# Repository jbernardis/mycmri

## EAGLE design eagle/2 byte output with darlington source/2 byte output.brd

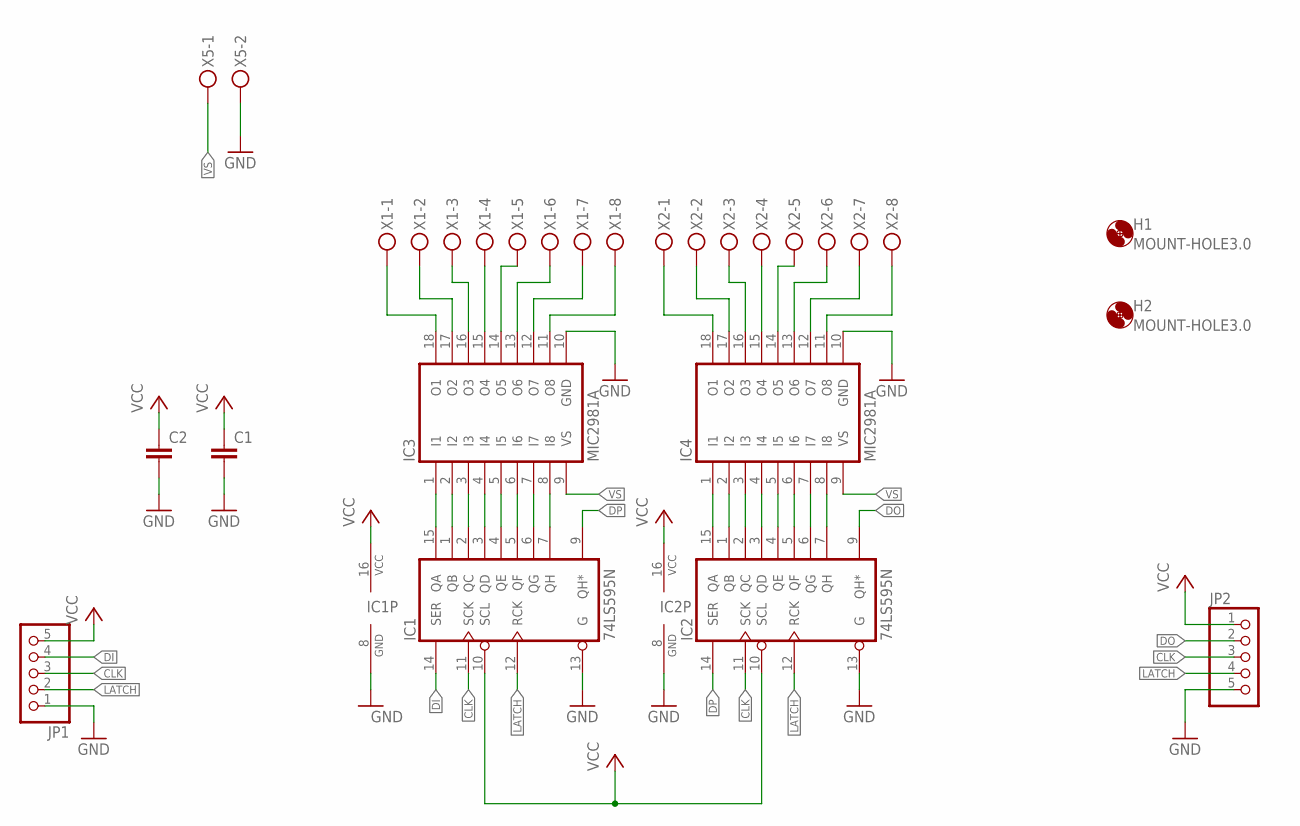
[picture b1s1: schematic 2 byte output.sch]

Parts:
C1, C2: C-EU050-035X075; C050-035X075
H1, H2: MOUNT-HOLE3.0; 3,0
IC1, IC2: 74LS595N; DIL16
IC3, IC4: MIC2981A; DIL18
JP1, JP2: PINHD-1X5/90; 1X05/90
X1, X2: MKDSN1,5/8-5,08
X5: MKDSN1,5/2-5,08

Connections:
CLK: IC1.11 (SCK), IC2.11 (SCK), JP1.3, JP2.3
DI: IC1.14 (SER), JP1.4
DO: IC2.9 (QH*), JP2.2
DP: IC1.9 (QH*), IC2.14 (SER)
GND: C1.2, C2.2, IC1.8 (GND), IC1.13 (G), IC2.8 (GND), IC2.13 (G), IC3.10 (GND), IC4.10 (GND), JP1.1, JP2.5, X5.2
LATCH: IC1.12 (RCK), IC2.12 (RCK), JP1.2, JP2.4
unnamed: IC3.15 (O4), X1.4
unnamed: IC3.16 (O3), X1.3
unnamed: IC3.17 (O2), X1.2
unnamed: IC3.18 (O1), X1.1
unnamed: IC3.14 (O5), X1.5
unnamed: IC3.12 (O7), X1.7
unnamed: IC3.11 (O8), X1.8
unnamed: IC3.13 (O6), X1.6
unnamed: IC4.15 (O4), X2.4
unnamed: IC4.16 (O3), X2.3
unnamed: IC4.17 (O2), X2.2
unnamed: IC4.18 (O1), X2.1
unnamed: IC4.14 (O5), X2.5
unnamed: IC4.13 (O6), X2.6
unnamed: IC4.12 (O7), X2.7
unnamed: IC4.11 (O8), X2.8
unnamed: IC1.15 (QA), IC3.1 (I1)
unnamed: IC1.1 (QB), IC3.2 (I2)
unnamed: IC1.2 (QC), IC3.3 (I3)
unnamed: IC1.3 (QD), IC3.4 (I4)
unnamed: IC1.4 (QE), IC3.5 (I5)
unnamed: IC1.5 (QF), IC3.6 (I6)
unnamed: IC1.6 (QG), IC3.7 (I7)
unnamed: IC1.7 (QH), IC3.8 (I8)
unnamed: IC2.15 (QA), IC4.1 (I1)
unnamed: IC2.1 (QB), IC4.2 (I2)
unnamed: IC2.2 (QC), IC4.3 (I3)
unnamed: IC2.3 (QD), IC4.4 (I4)
unnamed: IC2.4 (QE), IC4.5 (I5)
unnamed: IC2.5 (QF), IC4.6 (I6)
unnamed: IC2.6 (QG), IC4.7 (I7)
unnamed: IC2.7 (QH), IC4.8 (I8)
VCC: C1.1, C2.1, IC1.10 (SCL), IC1.16 (VCC), IC2.10 (SCL), IC2.16 (VCC), JP1.5, JP2.1
VS: IC3.9 (VS), IC4.9 (VS), X5.1

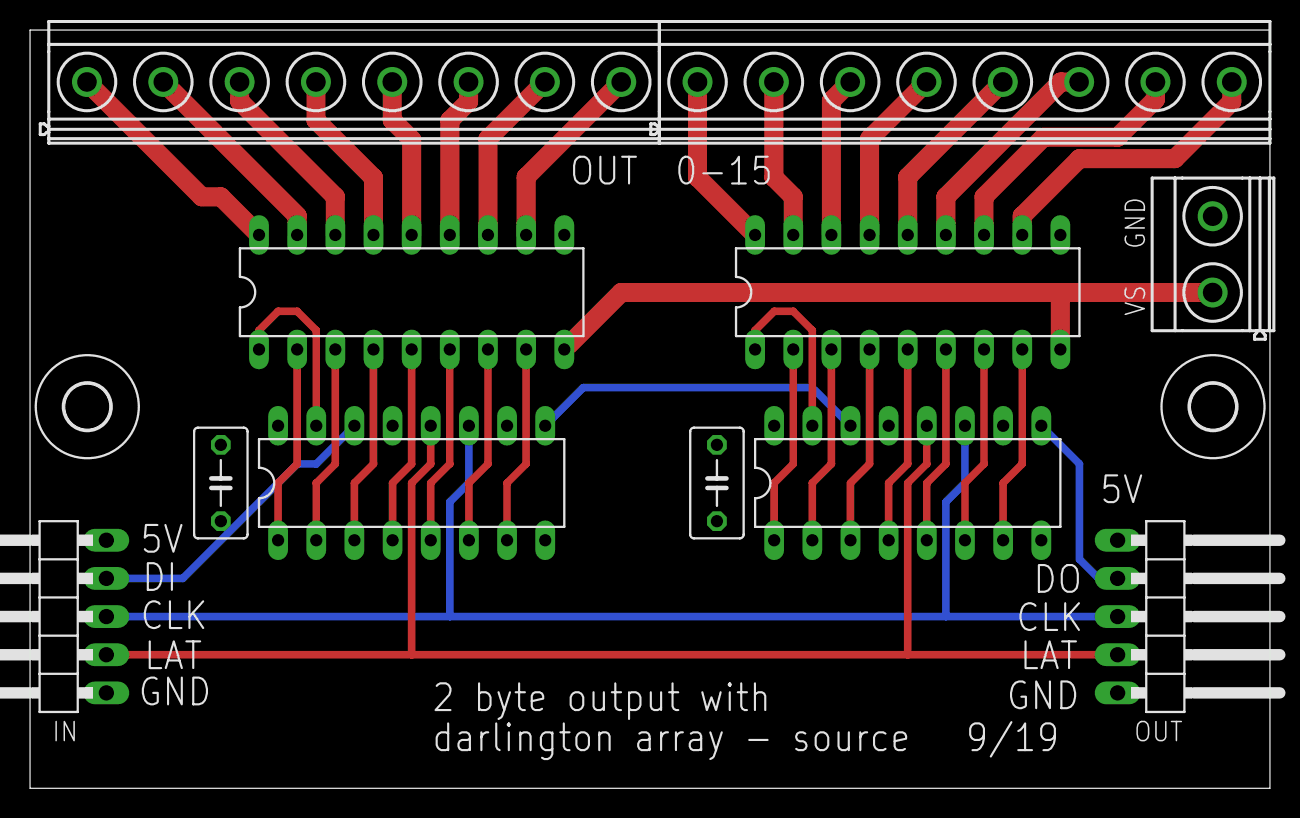
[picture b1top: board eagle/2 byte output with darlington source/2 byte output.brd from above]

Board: 2 copper layers, 82.5 x 50.5 mm, 13 parts (0 on the bottom side), 40 nets.

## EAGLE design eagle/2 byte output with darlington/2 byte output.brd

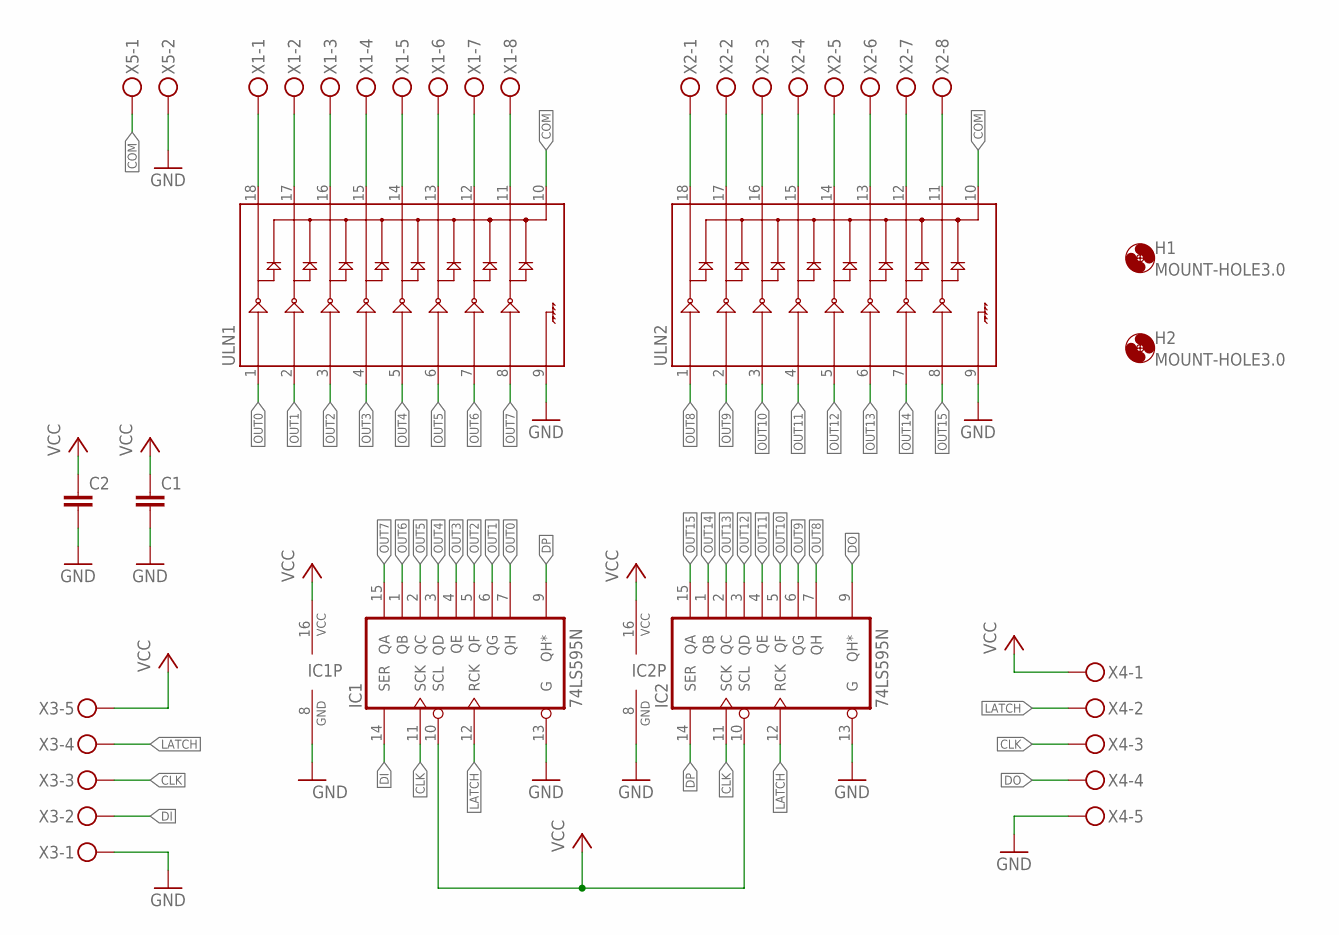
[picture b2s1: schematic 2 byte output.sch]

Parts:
C1, C2: C-EU050-035X075; C050-035X075
H1, H2: MOUNT-HOLE3.0; 3,0
IC1, IC2: 74LS595N; DIL16
ULN1, ULN2: ULN2803DIP; DIL18
X1, X2: MKDSN1,5/8-5,08
X3, X4: MKDSN1,5/5-5,08
X5: MKDSN1,5/2-5,08

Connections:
CLK: IC1.11 (SCK), IC2.11 (SCK), X3.3, X4.3
COM: ULN1.10, ULN2.10, X5.1
DI: IC1.14 (SER), X3.2
DO: IC2.9 (QH*), X4.4
DP: IC1.9 (QH*), IC2.14 (SER)
GND: C1.2, C2.2, IC1.8 (GND), IC1.13 (G), IC2.8 (GND), IC2.13 (G), ULN1.9, ULN2.9, X3.1, X4.5, X5.2
LATCH: IC1.12 (RCK), IC2.12 (RCK), X3.4, X4.2
unnamed: ULN1.18, X1.1
unnamed: ULN1.17, X1.2
unnamed: ULN1.16, X1.3
unnamed: ULN1.15, X1.4
unnamed: ULN1.14, X1.5
unnamed: ULN1.13, X1.6
unnamed: ULN1.12, X1.7
unnamed: ULN1.11, X1.8
unnamed: ULN2.18, X2.1
unnamed: ULN2.17, X2.2
unnamed: ULN2.16, X2.3
unnamed: ULN2.15, X2.4
unnamed: ULN2.14, X2.5
unnamed: ULN2.13, X2.6
unnamed: ULN2.12, X2.7
unnamed: ULN2.11, X2.8
OUT0: IC1.7 (QH), ULN1.1
OUT1: IC1.6 (QG), ULN1.2
OUT2: IC1.5 (QF), ULN1.3
OUT3: IC1.4 (QE), ULN1.4
OUT4: IC1.3 (QD), ULN1.5
OUT5: IC1.2 (QC), ULN1.6
OUT6: IC1.1 (QB), ULN1.7
OUT7: IC1.15 (QA), ULN1.8
OUT8: IC2.7 (QH), ULN2.1
OUT9: IC2.6 (QG), ULN2.2
OUT10: IC2.5 (QF), ULN2.3
OUT11: IC2.4 (QE), ULN2.4
OUT12: IC2.3 (QD), ULN2.5
OUT13: IC2.2 (QC), ULN2.6
OUT14: IC2.1 (QB), ULN2.7
OUT15: IC2.15 (QA), ULN2.8
VCC: C1.1, C2.1, IC1.10 (SCL), IC1.16 (VCC), IC2.10 (SCL), IC2.16 (VCC), X3.5, X4.1

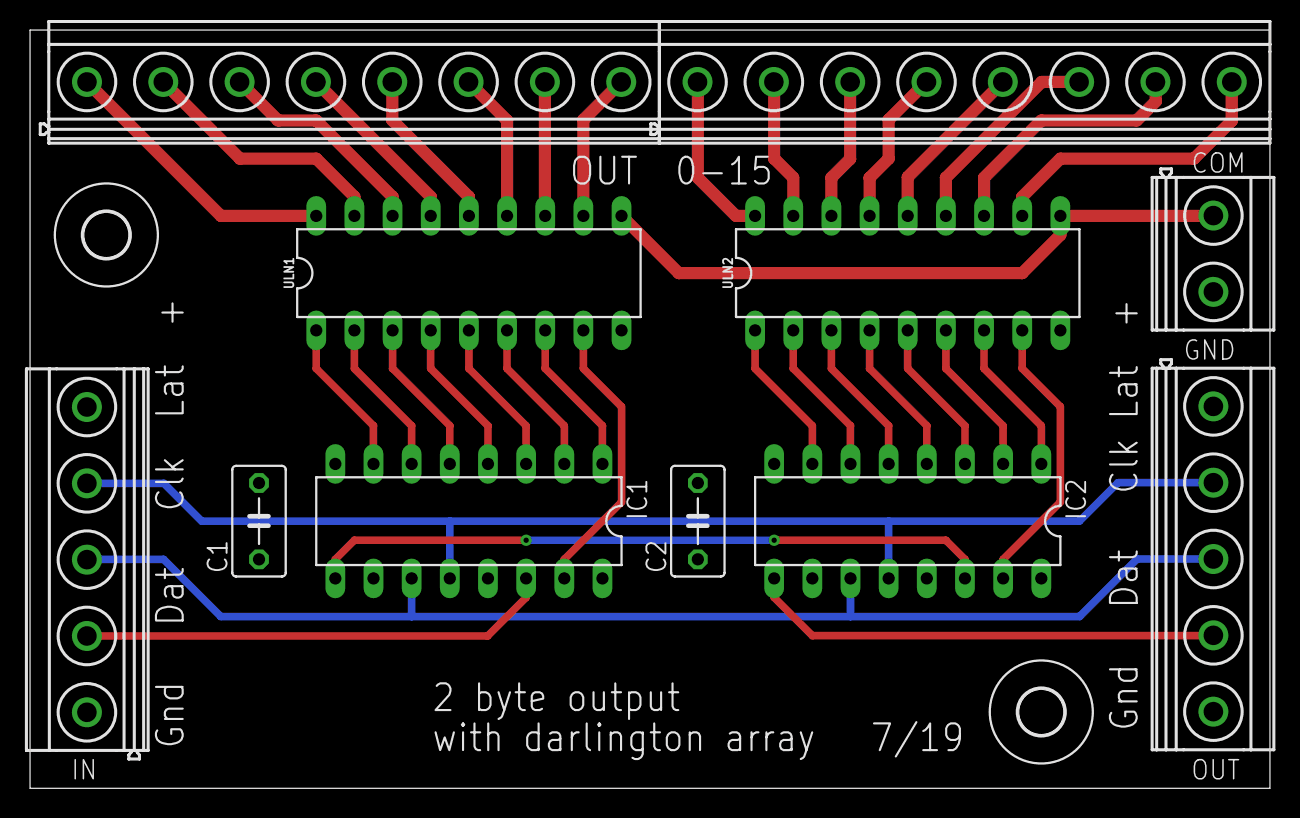
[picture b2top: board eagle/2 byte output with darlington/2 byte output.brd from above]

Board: 2 copper layers, 82.5 x 50.5 mm, 13 parts (0 on the bottom side), 40 nets.

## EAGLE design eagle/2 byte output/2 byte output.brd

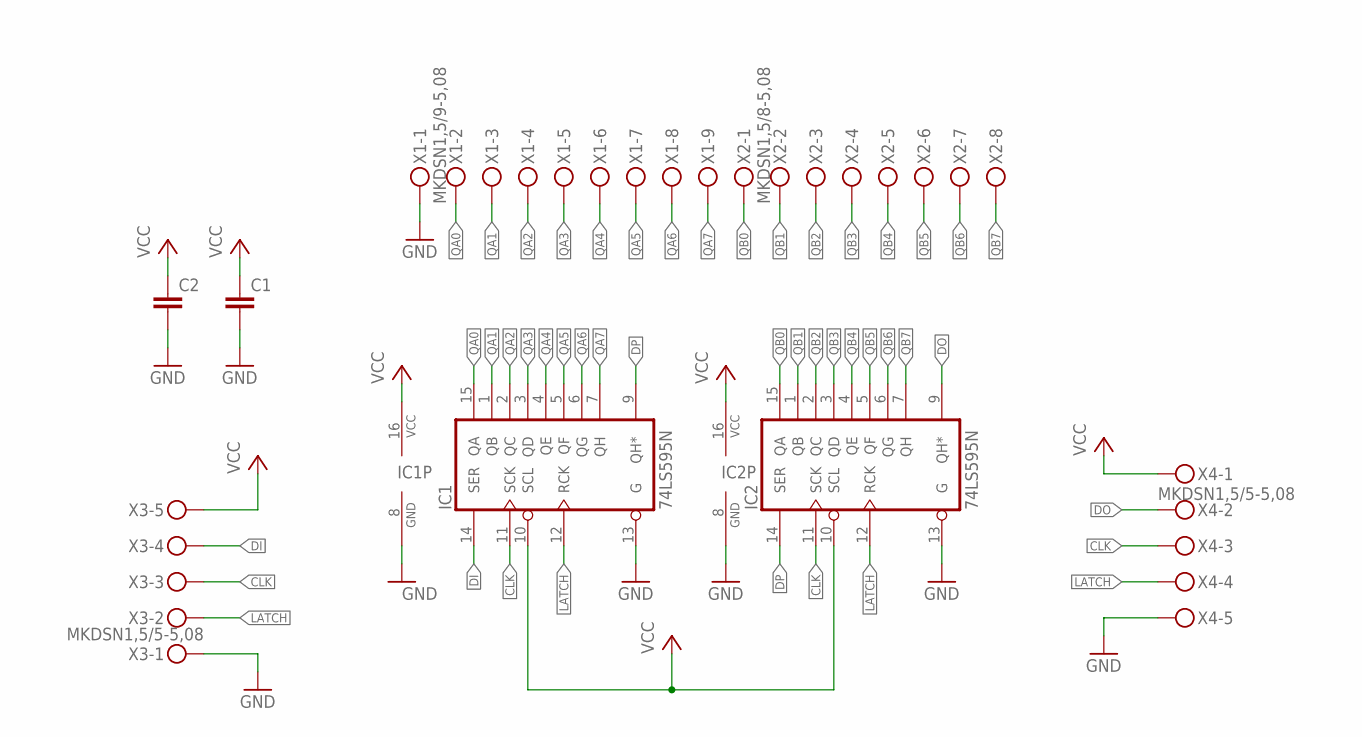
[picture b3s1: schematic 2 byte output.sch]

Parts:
C1, C2: C-EU050-035X075; C050-035X075
IC1, IC2: 74LS595N; DIL16
X1: MKDSN1,5/9-5,08
X2: MKDSN1,5/8-5,08
X3, X4: MKDSN1,5/5-5,08

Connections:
CLK: IC1.11 (SCK), IC2.11 (SCK), X3.3, X4.3
DI: IC1.14 (SER), X3.4
DO: IC2.9 (QH*), X4.2
DP: IC1.9 (QH*), IC2.14 (SER)
GND: C1.2, C2.2, IC1.8 (GND), IC1.13 (G), IC2.8 (GND), IC2.13 (G), X1.1, X3.1, X4.5
LATCH: IC1.12 (RCK), IC2.12 (RCK), X3.2, X4.4
QA0: IC1.15 (QA), X1.2
QA1: IC1.1 (QB), X1.3
QA2: IC1.2 (QC), X1.4
QA3: IC1.3 (QD), X1.5
QA4: IC1.4 (QE), X1.6
QA5: IC1.5 (QF), X1.7
QA6: IC1.6 (QG), X1.8
QA7: IC1.7 (QH), X1.9
QB0: IC2.15 (QA), X2.1
QB1: IC2.1 (QB), X2.2
QB2: IC2.2 (QC), X2.3
QB3: IC2.3 (QD), X2.4
QB4: IC2.4 (QE), X2.5
QB5: IC2.5 (QF), X2.6
QB6: IC2.6 (QG), X2.7
QB7: IC2.7 (QH), X2.8
VCC: C1.1, C2.1, IC1.10 (SCL), IC1.16 (VCC), IC2.10 (SCL), IC2.16 (VCC), X3.5, X4.1

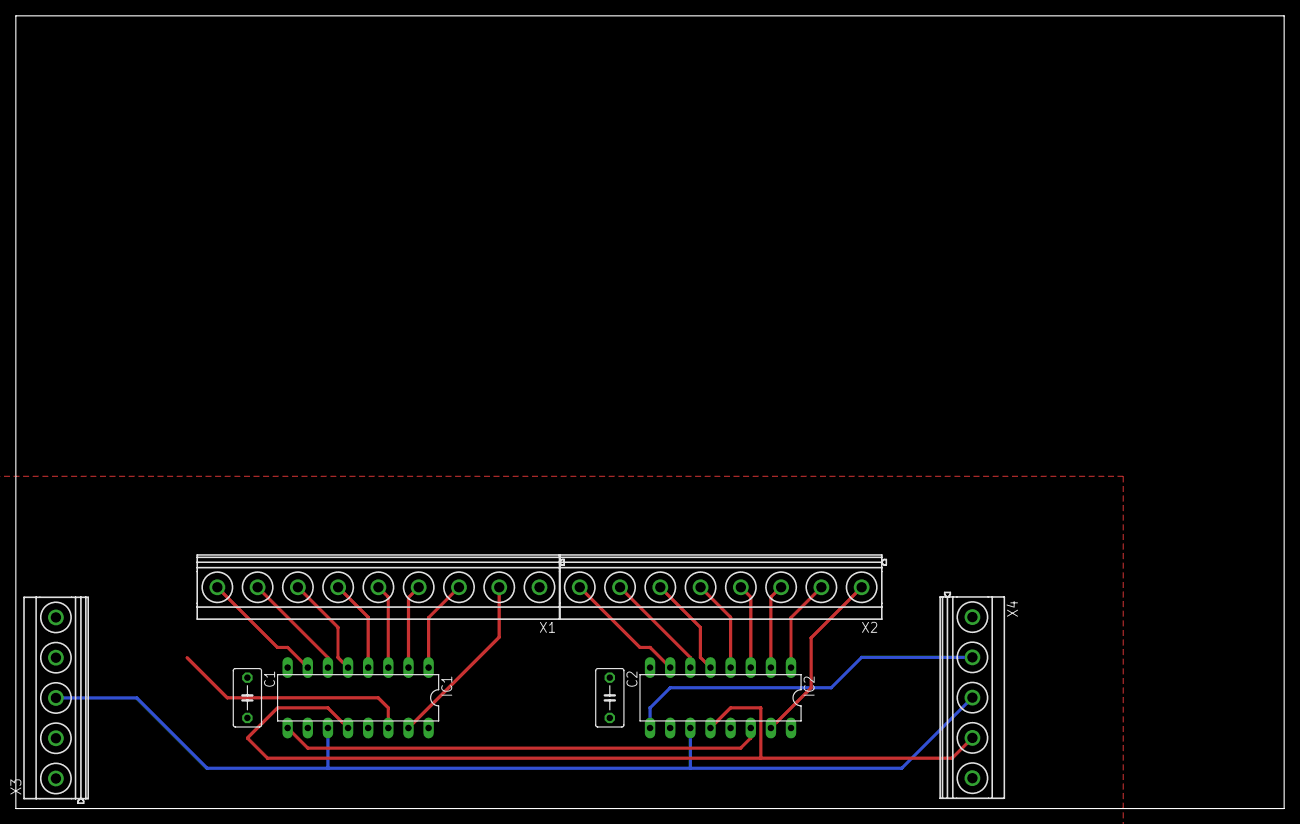
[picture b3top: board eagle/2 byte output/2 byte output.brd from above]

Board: 2 copper layers, 160.0 x 100.0 mm, 8 parts (0 on the bottom side), 23 nets.

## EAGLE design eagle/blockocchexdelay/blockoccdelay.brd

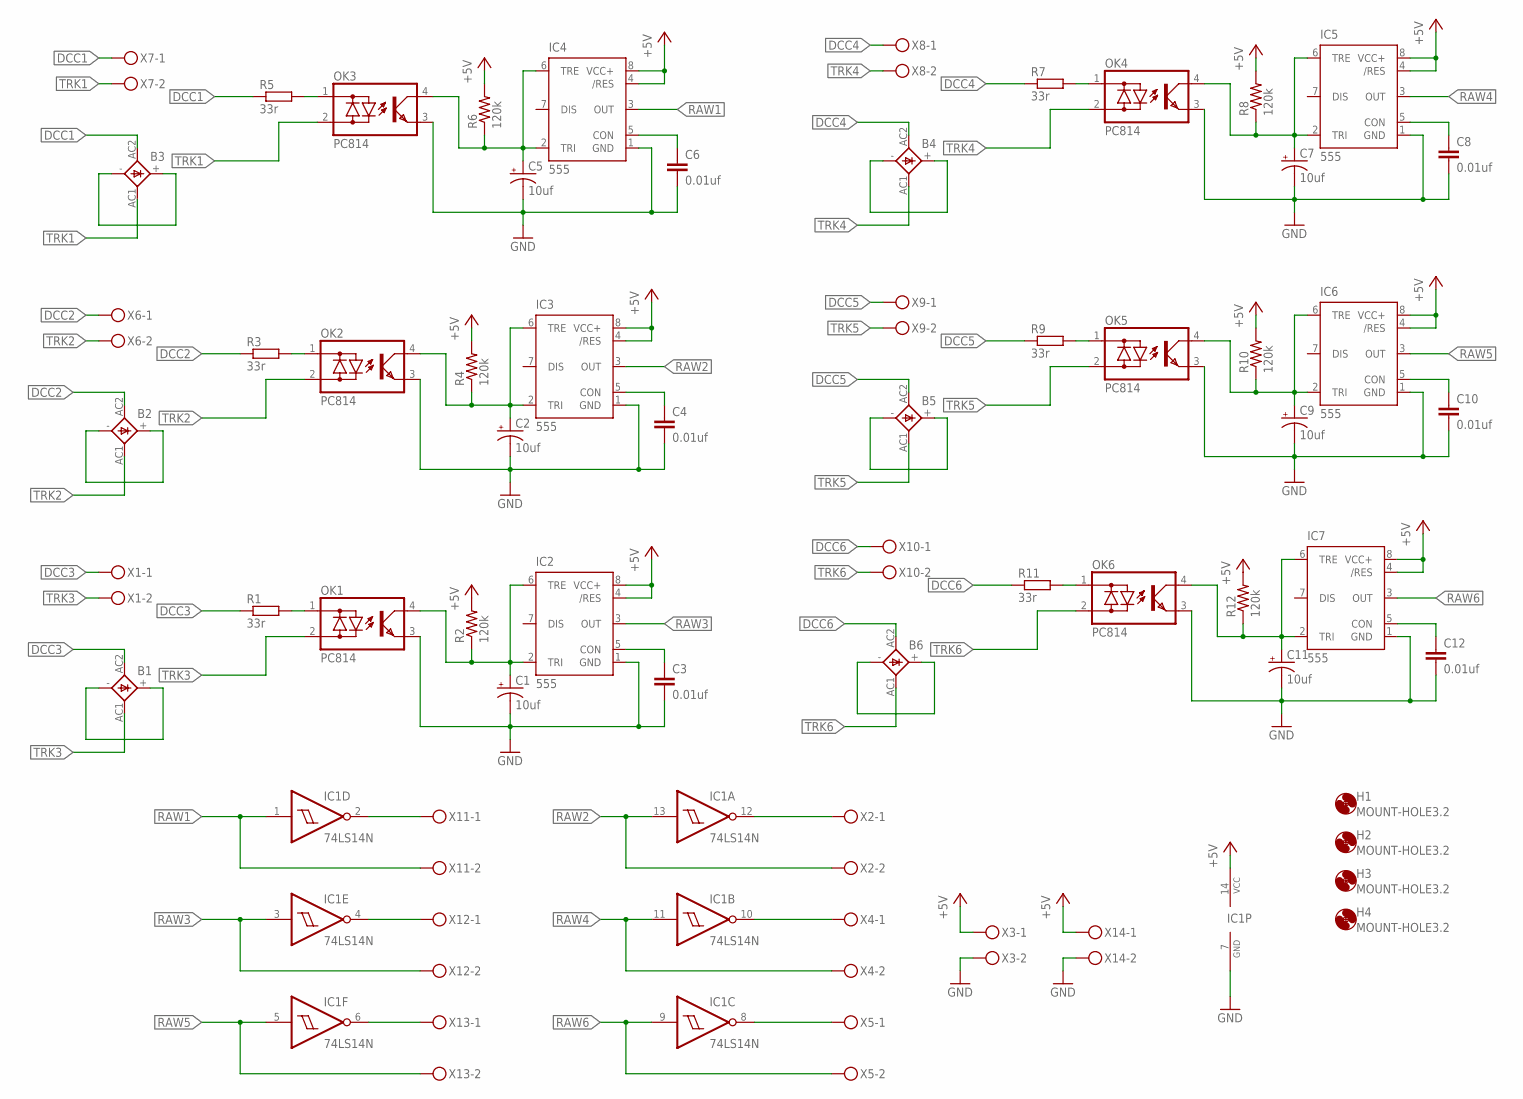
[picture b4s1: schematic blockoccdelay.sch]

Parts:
B1, B2, B3, B4, B5, B6: GBU4; GBU4S
C1, C2, C5, C7, C9, C11: 10uf; E2,5-6
C3, C4, C6, C8, C10, C12: 0.01uf; C050-035X075
H1, H2, H3, H4: MOUNT-HOLE3.2; 3,2
IC1: 74LS14N; DIL14
IC2, IC3, IC4, IC5, IC6, IC7: 555; DIP08
OK1, OK2, OK3, OK4, OK5, OK6: PC814; DIL04
R1, R3, R5, R7, R9, R11: 33r; 0207/2V
R2, R4, R6, R8, R10, R12: 120k; 0309V
X1, X2, X3, X4, X5, X6, X7, X8, X9, X10, X11, X12, X13, X14: MKDSN1,5/2-5,08

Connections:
+5V: IC1.14 (VCC), IC2.4 (/RES), IC2.8 (VCC+), IC3.4 (/RES), IC3.8 (VCC+), IC4.4 (/RES), IC4.8 (VCC+), IC5.4 (/RES), IC5.8 (VCC+), IC6.4 (/RES), IC6.8 (VCC+), IC7.4 (/RES), IC7.8 (VCC+), R2.2, R4.2, R6.2, R8.2, R10.2, R12.2, X3.1, X14.1
DCC1: B3.AC2 (AC1), R5.1, X7.1
DCC2: B2.AC2 (AC1), R3.1, X6.1
DCC3: B1.AC2 (AC1), R1.1, X1.1
DCC4: B4.AC2 (AC1), R7.1, X8.1
DCC5: B5.AC2 (AC1), R9.1, X9.1
DCC6: B6.AC2 (AC1), R11.1, X10.1
GND: C1.-, C2.-, C3.2, C4.2, C5.-, C6.2, C7.-, C8.2, C9.-, C10.2, C11.-, C12.2, IC1.7 (GND), IC2.1 (GND), IC3.1 (GND), IC4.1 (GND), IC5.1 (GND), IC6.1 (GND), IC7.1 (GND), OK1.3 (E), OK2.3 (E), OK3.3 (E), OK4.3 (E), OK5.3 (E), OK6.3 (E), X3.2, X14.2
unnamed: B1.+, B1.-
unnamed: OK1.1 (AC1), R1.2
unnamed: C3.1, IC2.5 (CON)
unnamed: IC1.12 (O), X2.1
unnamed: B4.+, B4.-
unnamed: OK4.1 (AC1), R7.2
unnamed: IC1.10 (O), X4.1
unnamed: C8.1, IC5.5 (CON)
unnamed: IC1.8 (O), X5.1
unnamed: B2.+, B2.-
unnamed: OK2.1 (AC1), R3.2
unnamed: C4.1, IC3.5 (CON)
unnamed: B3.+, B3.-
unnamed: OK3.1 (AC1), R5.2
unnamed: C6.1, IC4.5 (CON)
unnamed: B5.+, B5.-
unnamed: OK5.1 (AC1), R9.2
unnamed: C10.1, IC6.5 (CON)
unnamed: B6.+, B6.-
unnamed: OK6.1 (AC1), R11.2
unnamed: C12.1, IC7.5 (CON)
unnamed: IC1.2 (O), X11.1
unnamed: IC1.4 (O), X12.1
unnamed: IC1.6 (O), X13.1
RAW1: IC1.1 (I), IC4.3 (OUT), X11.2
RAW2: IC1.13 (I), IC3.3 (OUT), X2.2
RAW3: IC1.3 (I), IC2.3 (OUT), X12.2
RAW4: IC1.11 (I), IC5.3 (OUT), X4.2
RAW5: IC1.5 (I), IC6.3 (OUT), X13.2
RAW6: IC1.9 (I), IC7.3 (OUT), X5.2
TRI: C1.+, IC2.2 (TRI), IC2.6 (TRE), OK1.4 (C), R2.1
TRI1: C2.+, IC3.2 (TRI), IC3.6 (TRE), OK2.4 (C), R4.1
TRI2: C5.+, IC4.2 (TRI), IC4.6 (TRE), OK3.4 (C), R6.1
TRI3: C7.+, IC5.2 (TRI), IC5.6 (TRE), OK4.4 (C), R8.1
TRI4: C9.+, IC6.2 (TRI), IC6.6 (TRE), OK5.4 (C), R10.1
TRI5: C11.+, IC7.2 (TRI), IC7.6 (TRE), OK6.4 (C), R12.1
TRK1: B3.AC1 (AC2), OK3.2 (AC2), X7.2
TRK2: B2.AC1 (AC2), OK2.2 (AC2), X6.2
TRK3: B1.AC1 (AC2), OK1.2 (AC2), X1.2
TRK4: B4.AC1 (AC2), OK4.2 (AC2), X8.2
TRK5: B5.AC1 (AC2), OK5.2 (AC2), X9.2
TRK6: B6.AC1 (AC2), OK6.2 (AC2), X10.2

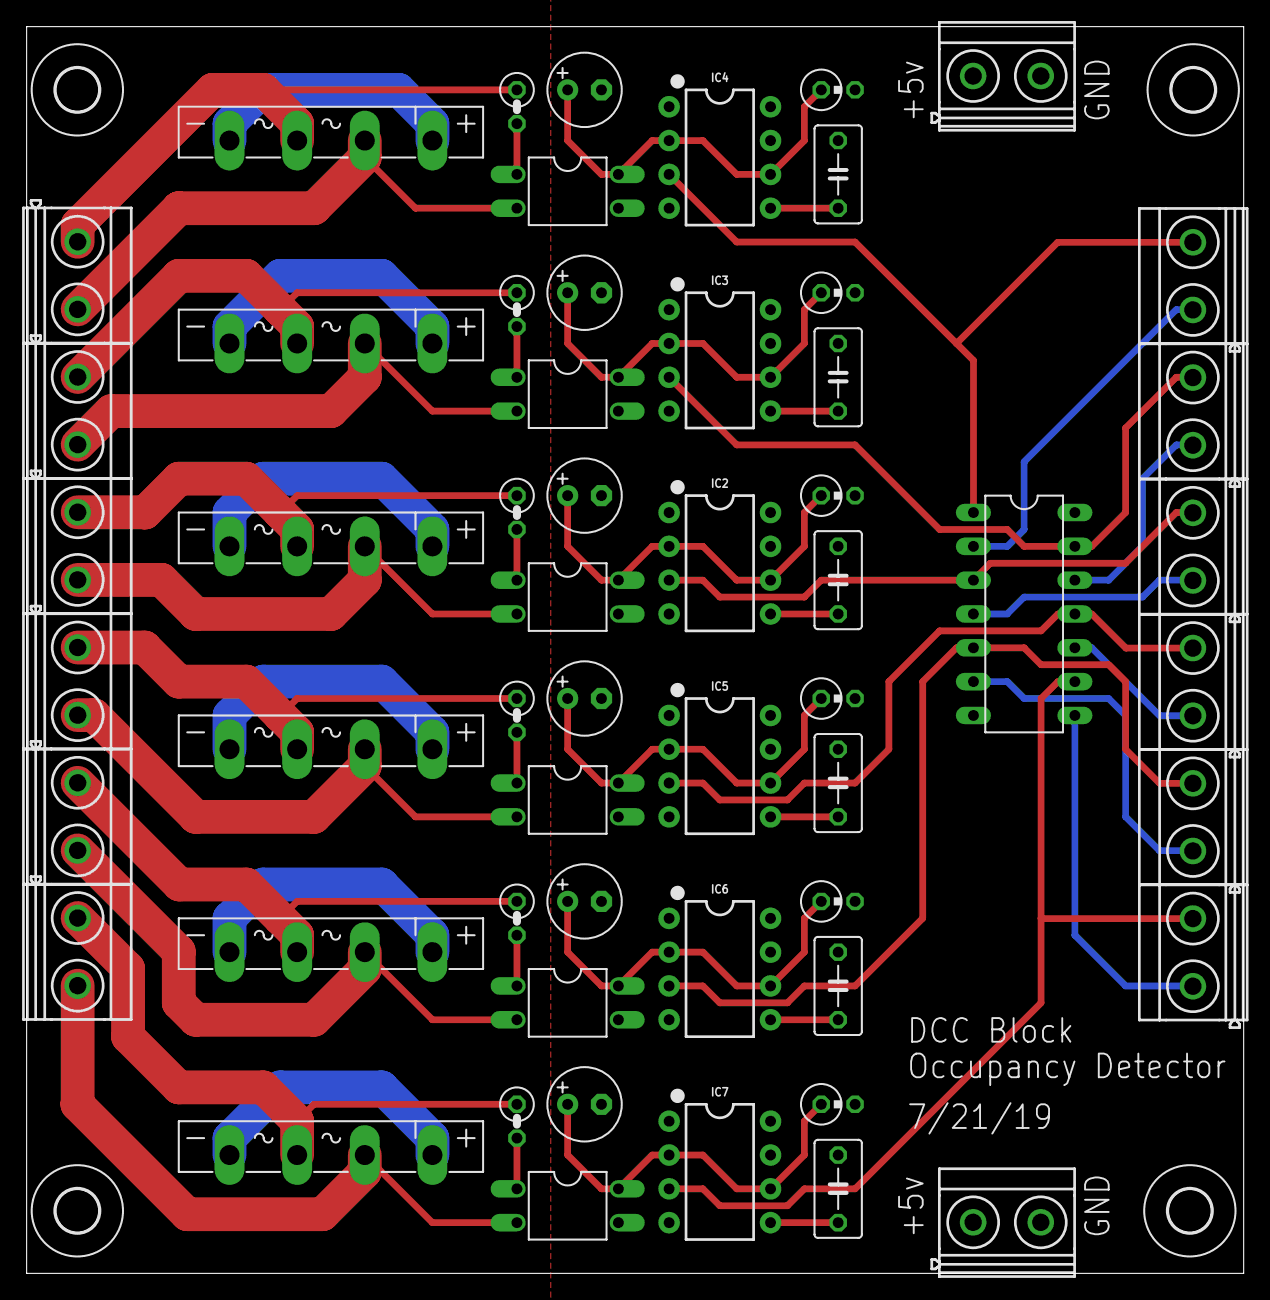
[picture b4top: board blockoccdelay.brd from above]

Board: 2 copper layers, 91.4 x 93.7 mm, 61 parts (0 on the bottom side), 50 nets.

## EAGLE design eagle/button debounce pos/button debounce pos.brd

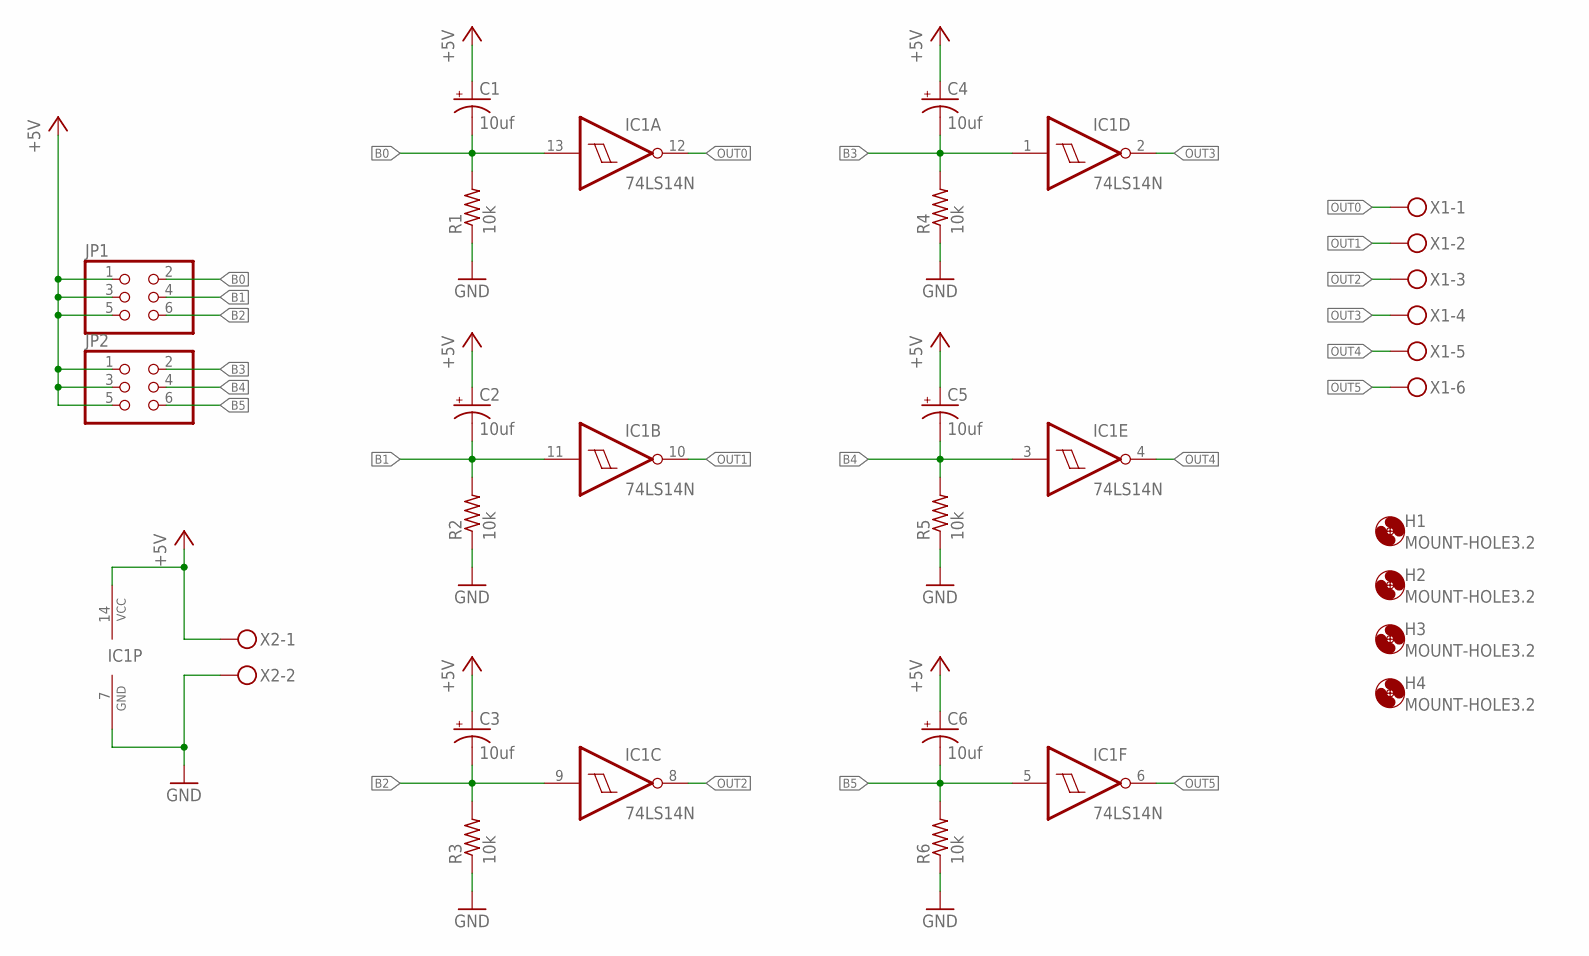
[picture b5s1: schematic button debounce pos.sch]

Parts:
C1, C2, C3, C4, C5, C6: 10uf; E2-5
H1, H2, H3, H4: MOUNT-HOLE3.2; 3,2
IC1: 74LS14N; DIL14
JP1, JP2: PINHD-2X3; 2X03
R1, R2, R3, R4, R5, R6: 10k; 0207/2V
X1: MKDSN1,5/6-5,08
X2: MKDSN1,5/2-5,08

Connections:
+5V: C1.+, C2.+, C3.+, C4.+, C5.+, C6.+, IC1.14 (VCC), JP1.1, JP1.3, JP1.5, JP2.1, JP2.3, JP2.5, X2.1
B0: C1.-, IC1.13 (I), JP1.2, R1.2
B1: C2.-, IC1.11 (I), JP1.4, R2.2
B2: C3.-, IC1.9 (I), JP1.6, R3.2
B3: C4.-, IC1.1 (I), JP2.2, R4.2
B4: C5.-, IC1.3 (I), JP2.4, R5.2
B5: C6.-, IC1.5 (I), JP2.6, R6.2
GND: IC1.7 (GND), R1.1, R2.1, R3.1, R4.1, R5.1, R6.1, X2.2
OUT0: IC1.12 (O), X1.1
OUT1: IC1.10 (O), X1.2
OUT2: IC1.8 (O), X1.3
OUT3: IC1.2 (O), X1.4
OUT4: IC1.4 (O), X1.5
OUT5: IC1.6 (O), X1.6

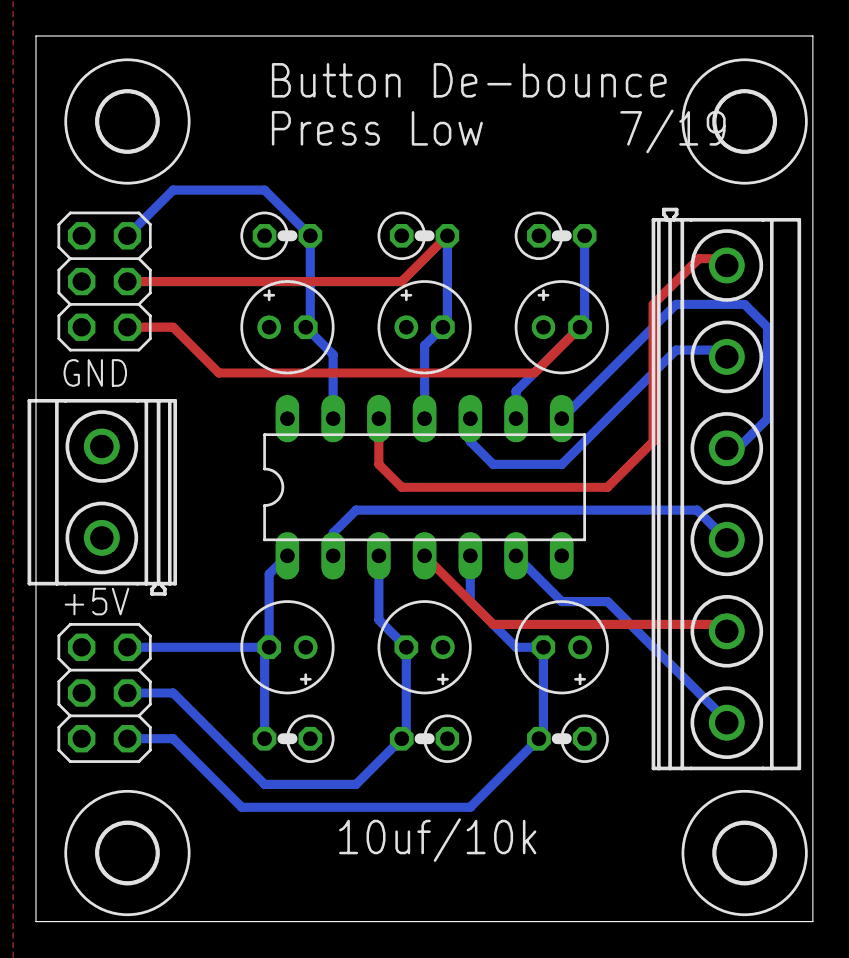
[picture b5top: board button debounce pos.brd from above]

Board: 2 copper layers, 43.2 x 49.2 mm, 21 parts (0 on the bottom side), 14 nets.

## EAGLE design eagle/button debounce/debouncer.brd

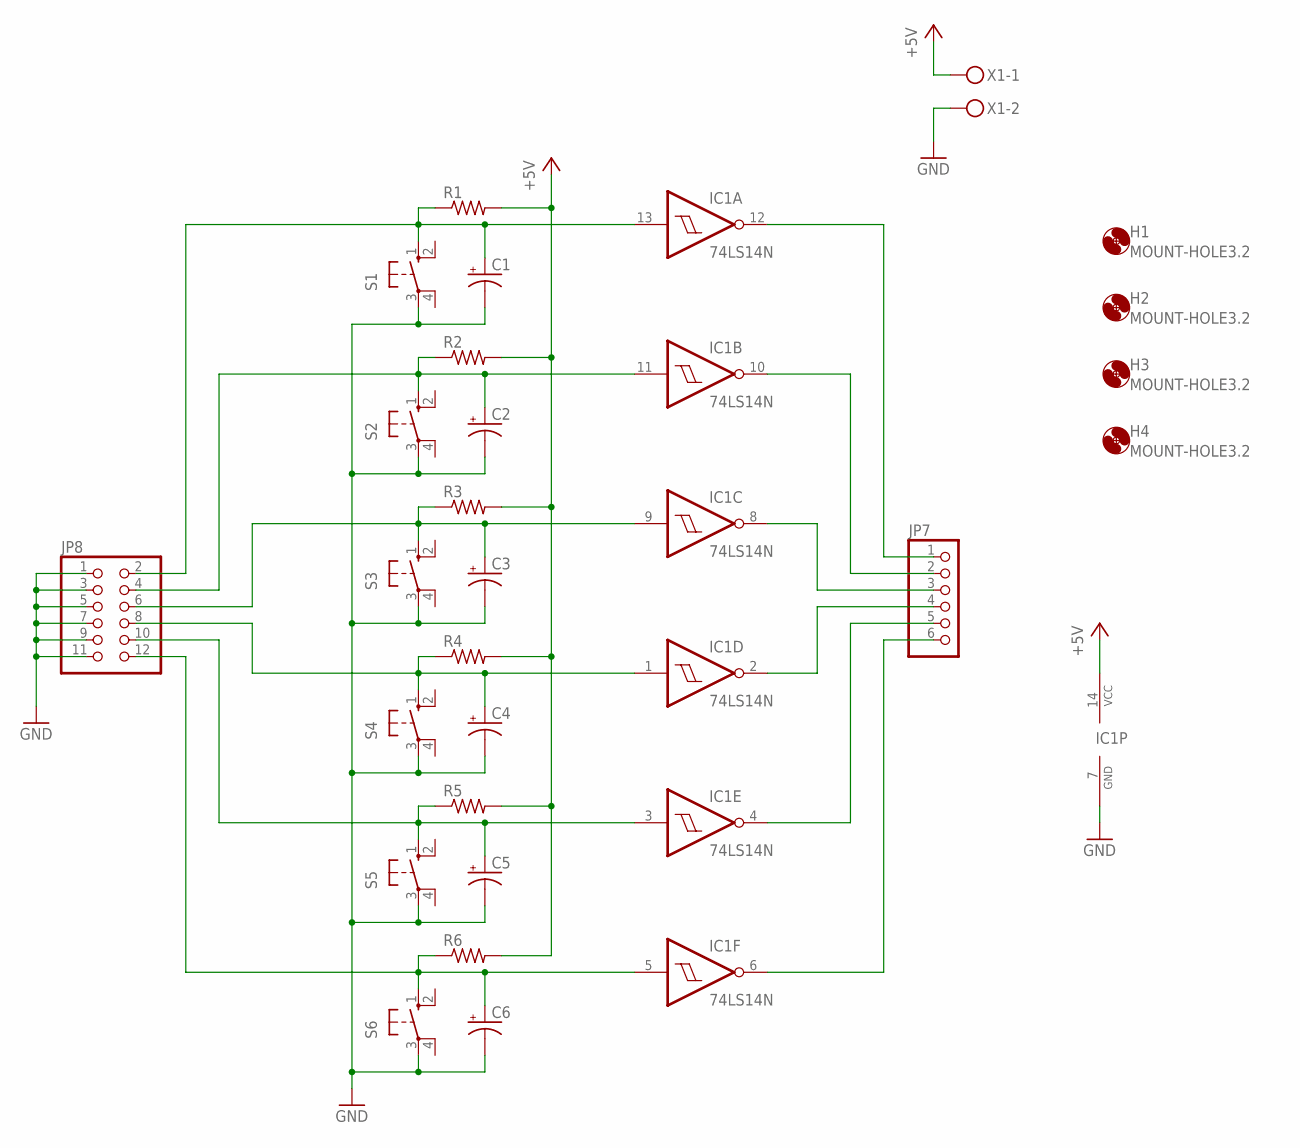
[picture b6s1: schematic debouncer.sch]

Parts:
C1, C2, C3, C4, C5, C6: CPOL-USE2-5; E2-5
H1, H2, H3, H4: MOUNT-HOLE3.2; 3,2
IC1: 74LS14N; DIL14
JP7: PINHD-1X6; 1X06
JP8: PINHD-2X6; 2X06
R1, R2, R3, R4, R5, R6: R-US_0207/12; 0207/12
S1, S2, S3, S4, S5, S6: 10-XX; B3F-10XX
X1: MKDSN1,5/2-5,08

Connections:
+5V: IC1.14 (VCC), R1.2, R2.2, R3.2, R4.2, R5.2, R6.2, X1.1
GND: C1.-, C2.-, C3.-, C4.-, C5.-, C6.-, IC1.7 (GND), JP8.1, JP8.3, JP8.5, JP8.7, JP8.9, JP8.11, S1.3, S2.3, S3.3, S4.3, S5.3, S6.3, X1.2
unnamed: C1.+, IC1.13 (I), JP8.2, R1.1, S1.1 (S)
unnamed: IC1.6 (O), JP7.6
unnamed: IC1.4 (O), JP7.5
unnamed: IC1.2 (O), JP7.4
unnamed: C2.+, IC1.11 (I), JP8.4, R2.1, S2.1 (S)
unnamed: IC1.8 (O), JP7.3
unnamed: IC1.10 (O), JP7.2
unnamed: C3.+, IC1.9 (I), JP8.6, R3.1, S3.1 (S)
unnamed: IC1.12 (O), JP7.1
unnamed: C4.+, IC1.1 (I), JP8.8, R4.1, S4.1 (S)
unnamed: C5.+, IC1.3 (I), JP8.10, R5.1, S5.1 (S)
unnamed: C6.+, IC1.5 (I), JP8.12, R6.1, S6.1 (S)

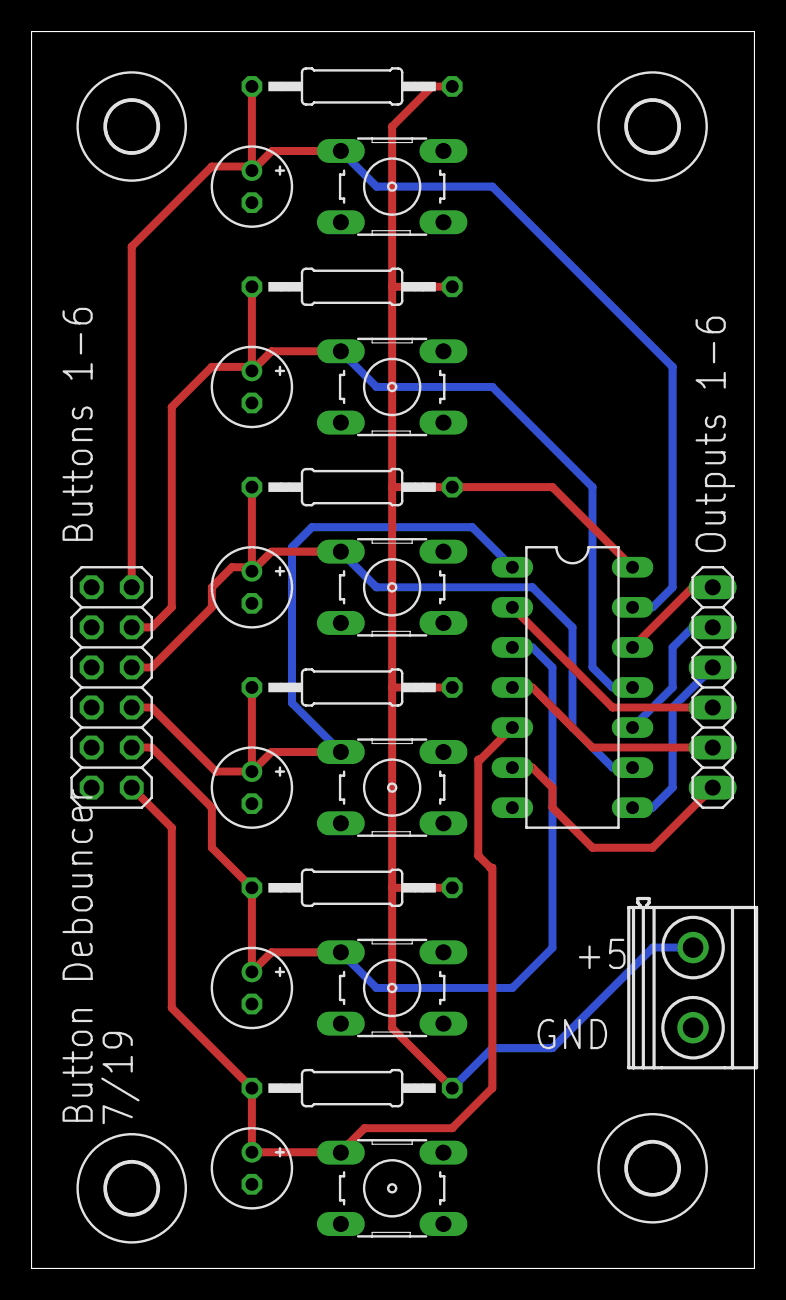
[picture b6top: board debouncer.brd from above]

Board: 2 copper layers, 45.8 x 78.4 mm, 26 parts (0 on the bottom side), 14 nets.

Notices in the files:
parts and their libraries:
SparkFun-IC-Special-Function: Licensing: Creative Commons ShareAlike 4.0 International - https://creativecommons.org/licenses/by-sa/4.0
